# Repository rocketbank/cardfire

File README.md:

# pan-scanner
Сканит PAN карты и вводит притворяясь клавиатурой

[Все в Notion ](https://www.notion.so/rocketguys/CardFire-PAN-Scanner-b663bdf931e24fb18de7a37c51332b52)

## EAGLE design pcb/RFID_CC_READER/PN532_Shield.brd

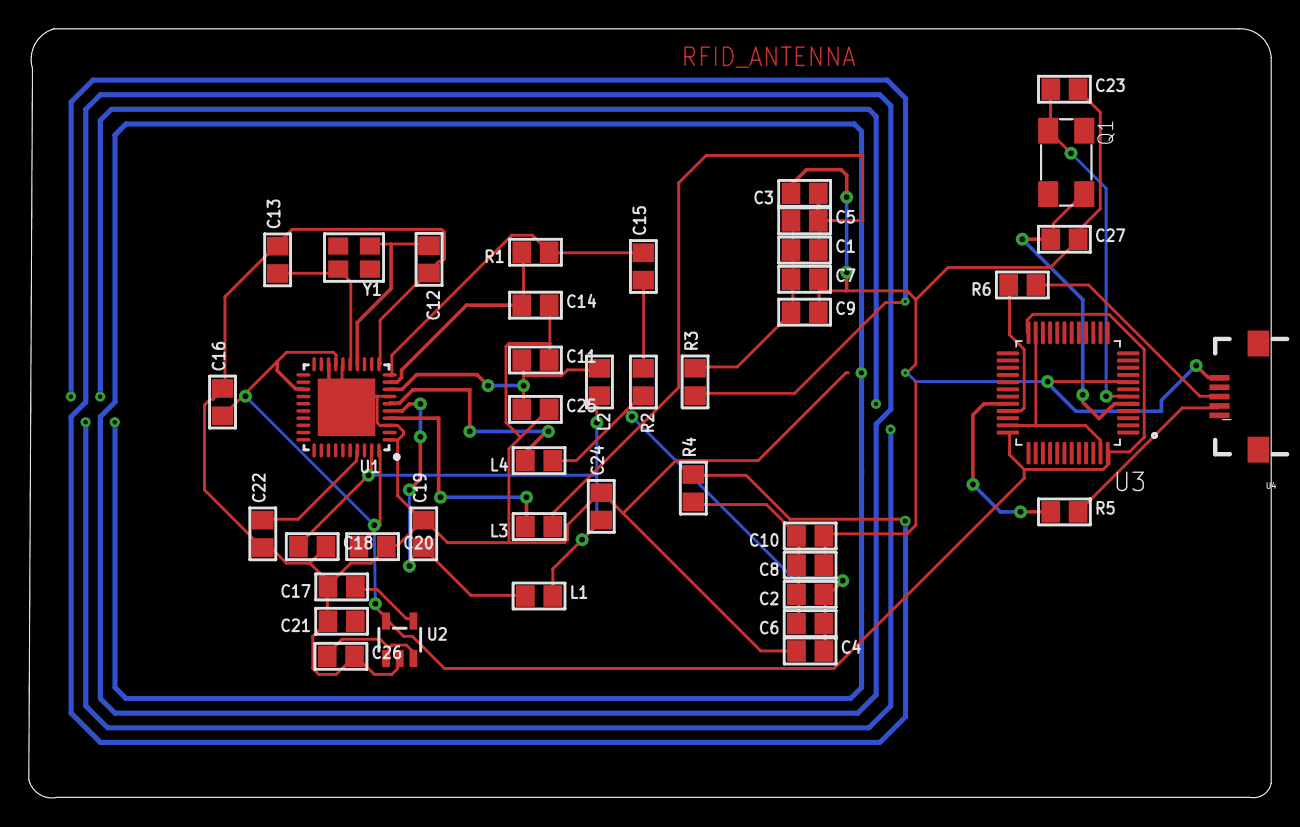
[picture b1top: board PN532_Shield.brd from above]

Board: 2 copper layers, 86.2 x 53.4 mm, 44 parts (0 on the bottom side), 29 nets.

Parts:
C1, C2: 22pF; 0805
C3, C4: 220pF; 0805
C5, C6, C9, C10: NC; 0805
C7, C8: 100pF; 0805
C11, C14, C16, C17, C20, C24: 0.1µF; 0805
C12, C13, C23, C27: 33pF; 0805
C15: 1000pF; 0805
C18, C19, C21, C22, C25, C26: 10µF; 0805
L1, L2: FERRITE; 0805
L3, L4: 560nH; 0805
L5: RFID_ANTENNA; ANTENNA
Q1: 6.0X3.5_4
R1, R5, R6: 1.0K; 0805
R2: 1.69K; 0805
R3, R4: 1.5; 0805
U1: PN532; HVQFN40-6X6
U2: ADP122(3.3V); SOT23-5
U3: STM32F103C8T6; QFP50P900X900X160-48N
U4: USB-MICRO-SMD
Y1: 27.12MHz; CRYSTAL_3.2X2.5

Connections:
5.0V: C26.1, U2.1, U2.3
GND: C4.1, C11.2, C12.2, C13.2, C14.2, C16.2, C17.2, C18.2, C19.2, C20.2, C21.2, C22.1, C24.2, C25.2, C26.2, U1.1, U1.3, U1.7, U1.11, U1.16, U1.18, U1.TP, U2.2
unnamed: L3.2, U1.4
unnamed: C1.2, C3.1, C5.2, L3.1
unnamed: L5.RIGHT_PIN, R3.1
unnamed: L5.LEFT_PIN, R4.2
unnamed: R5.1, U3.32
unnamed: C12.1, U1.14, Y1.1
unnamed: C13.1, U1.15, Y1.2
unnamed: C15.1, R2.1
unnamed: C14.1, R1.2, U1.9
unnamed: C15.2, R1.1, U1.10
unnamed: C2.1, C4.2, C6.1, L4.1, R2.2
unnamed: C11.1, C25.1, L2.1, U1.8
unnamed: C19.1, L1.1, U1.5
unnamed: R6.2, U3.33
unnamed: R5.2, U4.D-1
unnamed: R6.1, U4.D+1
unnamed: C27.1, Q1.3, U3.5
unnamed: C23.1, Q1.1, U3.6
unnamed: C17.1, U2.4
unnamed: C22.2, U1.37
S$1: C3.2, C7.2, C9.2, C23.2, C27.2
S$3: C8.1, C10.1
TX1_ANTENNA: C1.1, C5.1, C7.1, C9.1, R3.2
TX2_ANTENNA: C2.2, C6.2, C8.2, C10.2, R4.1
VCC: C18.1, C24.1, L1.2, L2.2, U1.39
VDD: C16.1, C20.1, U1.17, U1.23, U1.40, U2.5, U3.24, U3.36, U3.48
VSS: U3.23, U3.35, U3.47

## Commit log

2019-02-02 add LAST4, Beep, DEBUG
2019-02-04 Create preferences.txt
    You can copy-paste it to
    ~/Library/Arduino15/preferences.txt
    may be...
2019-02-04 Create preferences.txt (#1)
    You can copy-paste it to
    ~/Library/Arduino15/preferences.txt
    may be...
2019-03-22 fixes + passive beeper
2019-04-03 tune
2019-04-04 pcb wip
2019-04-04 define Beeper type opt
2019-04-09 library updates
2019-04-10 v0.00002

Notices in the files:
parts and their libraries:
crystal-geyer_V1_0: Copyright: Geyer-Electronic
